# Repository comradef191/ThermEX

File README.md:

# ThermEX
A BlackPill powered expansion board for Klipper 3D printers, allowing the use of numerous additional Thermistors.

- Can be stacked ontop of or underneith Nyoomies using appropiate spacers
- OpenSource Hardware, licensed under the [OHLv2-S](https://opensource.org/license/cern-ohl-s)
- 10 thermistors wired directly to the STM32
- 16 additional thermistors wired up via 4 ADS1115 ICs
- Powered directly from the USB port
- Uses an ultra-low-noise [TPS7A2033](https://www.ti.com/product/TPS7A20/part-details/TPS7A2033PDBVR) 300mA 3.3v voltage regulator to power all expansion headers and the ADS1115s
- Features native support for the STM32F4x1 BlackPill, with the unused extra GPIO being broken out to a labelled expansion header alongside 3v3 & GND
- Breaks out the I2C2 & I2C3 busses to a pair of dedicated 4-pin JST-XH connectors
- Breaks out the SPI2 bus to a dedicated header, alongside PB12 to act as chip-select

# NOTICE
if you are ordering a batch of PCBs, please for the love of god please use the pre-made gerber files in the [Releases tab](https://github.com/comradef191/ThermEX/releases) instead of downloading the repo, ignoring KiCADs warning you haven't got [a font installed](https://github.com/ETBCOR/nasin-nanpa), and then exporting your own files which both have the I2C bus shorted out (rendering only 10 thermistor ports usable) due to the missing font breaking artwork on the copper layer plus has had markings crediting me destroyed.

## Vendors
UK / EU
- None... yet!

Contact me on Discord if you want to add yourself to this list!

## Bill of Materials
This BoM lists exclusively through-hole components, as SMD components will be assembled for you by JLCPCB
|  Component         |QTY | Cost  |  Comment               |  Sourcing URL                                                                                                |
|--------------------|----|-------|------------------------|--------------------------------------------------------------------------------------------------------------|
|JST-XH 2-Pin        | 26 | $0.39 | Thermistor Ports       | https://www.lcsc.com/product-detail/Wire-To-Board-Connector_DEALON-XH-D-2A_C5160911.html                     |
|JST-XH 4-Pin        | 2  | $0.52 | I2C Ports              | https://www.lcsc.com/product-detail/Wire-To-Board-Connector_JST-B4B-XH-A-LF-SN_C144395.html                  |
|2.54 Socket, 1x20   | 2  | $0.81 | STM32 Socket           | https://www.lcsc.com/product-detail/Female-Headers_Shenzhen-Kinghelm-Elec-KH-2-54FH-1X20P-H8-5_C2905423.html |
|2.54 Header, 2x5    | 3  | $0.40 | GPIO; Cut-Down for SPI | https://www.lcsc.com/product-detail/Pin-Headers_HanElectricity-2541WV-2x05P_C5383106.html                    |
|STM32F401 Blackpill | 1  | $3.25 | Main controller        | https://www.aliexpress.com/item/1005006127461676.html                                                        |

# Gallery
*As of 09APR25 no ThermEX26 boards have been produced, thus only KiCad Renders are present currently*

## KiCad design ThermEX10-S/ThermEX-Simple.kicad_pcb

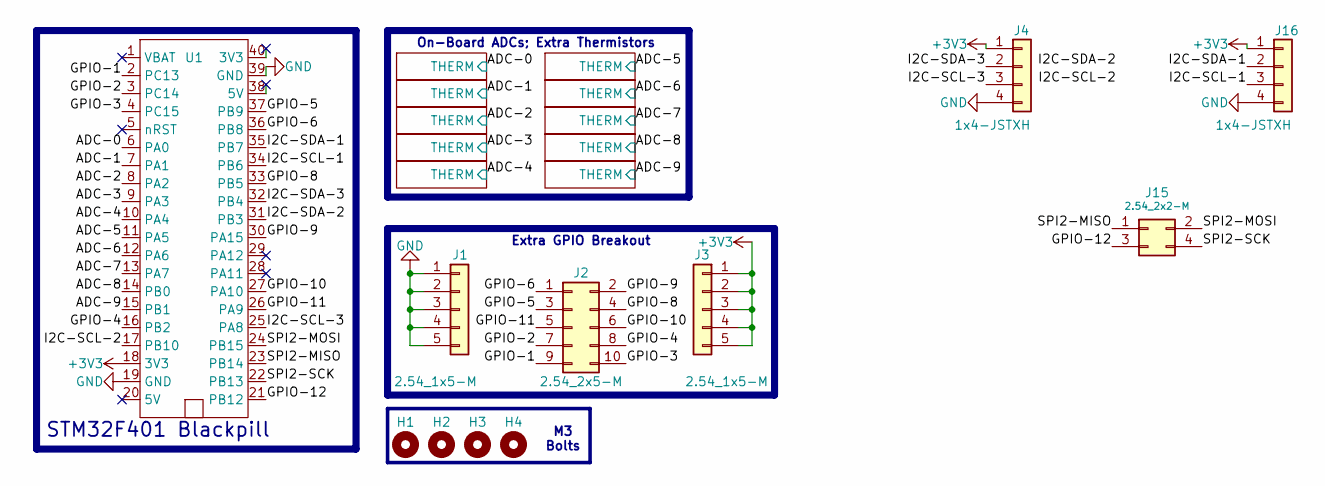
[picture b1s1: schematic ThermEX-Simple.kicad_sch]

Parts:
H1, H2, H3, H4: MountingHole; M3 Mounting Hole ~ Classic - No Keepout
J1, J3: 2.54_1x5-M; PinHeader_1x05_P2.54mm_Vertical
J2: 2.54_2x5-M; PinHeader_2x05_P2.54mm_Vertical
J4, J16: 1x4-JSTXH; JST_XH_B4B-XH-A_1x04_P2.50mm_Vertical
J15: 2.54_2x2-M; PinHeader_2x02_P2.54mm_Vertical
U1: STM32F401 Blackpill; Socketed MCU - STM32 BlackPill

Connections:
+3V3: J3.1, J3.2, J3.3, J3.4, J3.5, J4.1, J16.1, U1.18 (3V3); also elsewhere on the board
/ADC-0: U1.6 (PA0); also elsewhere on the board
/ADC-1: U1.7 (PA1); also elsewhere on the board
/ADC-2: U1.8 (PA2); also elsewhere on the board
/ADC-3: U1.9 (PA3); also elsewhere on the board
/ADC-4: U1.10 (PA4); also elsewhere on the board
/ADC-5: U1.11 (PA5); also elsewhere on the board
/ADC-6: U1.12 (PA6); also elsewhere on the board
/ADC-7: U1.13 (PA7); also elsewhere on the board
/ADC-8: U1.14 (PB0); also elsewhere on the board
/ADC-9: U1.15 (PB1); also elsewhere on the board
/GPIO-1: J2.9, U1.2 (PC13)
/GPIO-2: J2.7, U1.3 (PC14)
/GPIO-3: J2.10, U1.4 (PC15)
/GPIO-4: J2.8, U1.16 (PB2)
/GPIO-5: J2.3, U1.37 (PB9)
/GPIO-6: J2.1, U1.36 (PB8)
/GPIO-8: J2.4, U1.33 (PB5)
/GPIO-9: J2.2, U1.30 (PA15)
/GPIO-10: J2.6, U1.27 (PA10)
/GPIO-11: J2.5, U1.26 (PA9)
/GPIO-12: J15.3, U1.21 (PB12)
/I2C-SCL-1: J16.3, U1.34 (PB6)
/I2C-SCL-2: U1.17 (PB10)
/I2C-SCL-3: J4.3, U1.25 (PA8)
/I2C-SDA-1: J16.2, U1.35 (PB7)
/I2C-SDA-2: U1.31 (PB3)
/I2C-SDA-3: J4.2, U1.32 (PB4)
/SPI2-MISO: J15.1, U1.23 (PB14)
/SPI2-MOSI: J15.2, U1.24 (PB15)
/SPI2-SCK: J15.4, U1.22 (PB13)
GND: J1.1, J1.2, J1.3, J1.4, J1.5, J4.4, J16.4, U1.19 (GND), U1.39 (GND); also elsewhere on the board

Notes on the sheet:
STM32F401 Blackpill
M3 Bolts
Extra GPIO Breakout
On-Board ADCs; Extra Thermistors

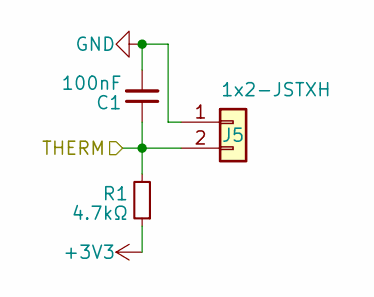
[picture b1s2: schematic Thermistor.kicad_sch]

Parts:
C1: 100nF; C_Disc_D5.0mm_W2.5mm_P5.00mm
J5: 1x2-JSTXH; JST-XH_1x02-V ~ Custom
R1: 4.7kΩ; R_Axial_DIN0207_L6.3mm_D2.5mm_P10.16mm_Horizontal

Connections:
+3V3: R1.1; also elsewhere on the board
/ADC-0: C1.1, J5.2, R1.2; also elsewhere on the board
GND: C1.2, J5.1; also elsewhere on the board

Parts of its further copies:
C2, C3, C4, C5, C6, C7, C8, C9, C10: 100nF; C_Disc_D5.0mm_W2.5mm_P5.00mm
J6, J7, J8, J9, J10, J11, J12, J13, J14: 1x2-JSTXH; JST-XH_1x02-V ~ Custom
R2, R3, R4, R5, R6, R7, R8, R9, R10: 4.7kΩ; R_Axial_DIN0207_L6.3mm_D2.5mm_P10.16mm_Horizontal

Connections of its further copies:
+3V3: R2.1, R3.1, R4.1, R5.1, R6.1, R7.1, R8.1, R9.1, R10.1; also elsewhere on the board
/ADC-1: C2.1, J6.2, R2.2; also elsewhere on the board
/ADC-2: C3.1, J7.2, R3.2; also elsewhere on the board
/ADC-3: C4.1, J8.2, R4.2; also elsewhere on the board
/ADC-4: C5.1, J9.2, R5.2; also elsewhere on the board
/ADC-5: C6.1, J10.2, R6.2; also elsewhere on the board
/ADC-6: C7.1, J11.2, R7.2; also elsewhere on the board
/ADC-7: C8.1, J12.2, R8.2; also elsewhere on the board
/ADC-8: C9.1, J13.2, R9.2; also elsewhere on the board
/ADC-9: C10.1, J14.2, R10.2; also elsewhere on the board
GND: C2.2, C3.2, C4.2, C5.2, C6.2, C7.2, C8.2, C9.2, C10.2, J6.1, J7.1, J8.1, J9.1, J10.1, J11.1, J12.1, J13.1, J14.1; also elsewhere on the board

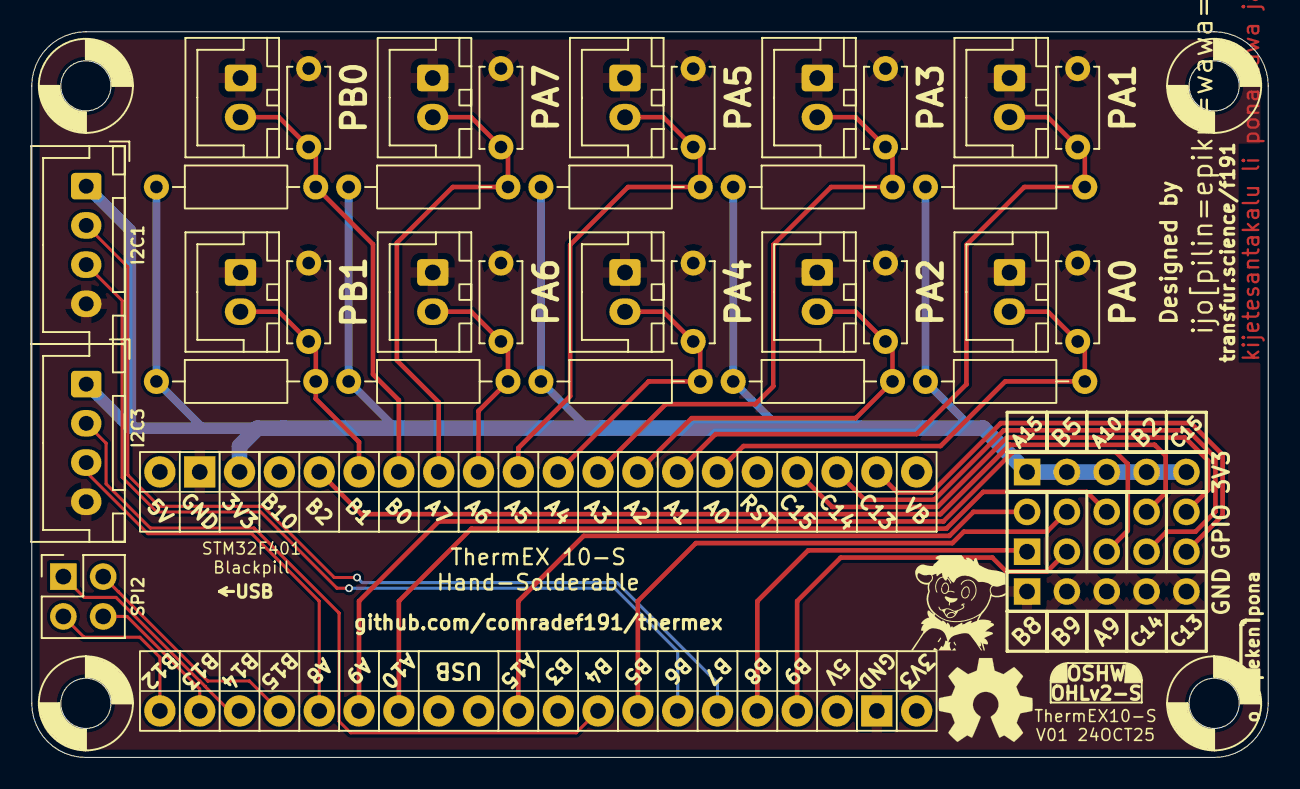
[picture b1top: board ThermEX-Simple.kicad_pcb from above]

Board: 2 copper layers, 78.9 x 46.3 mm, 41 parts (0 on the bottom side), 30 nets.

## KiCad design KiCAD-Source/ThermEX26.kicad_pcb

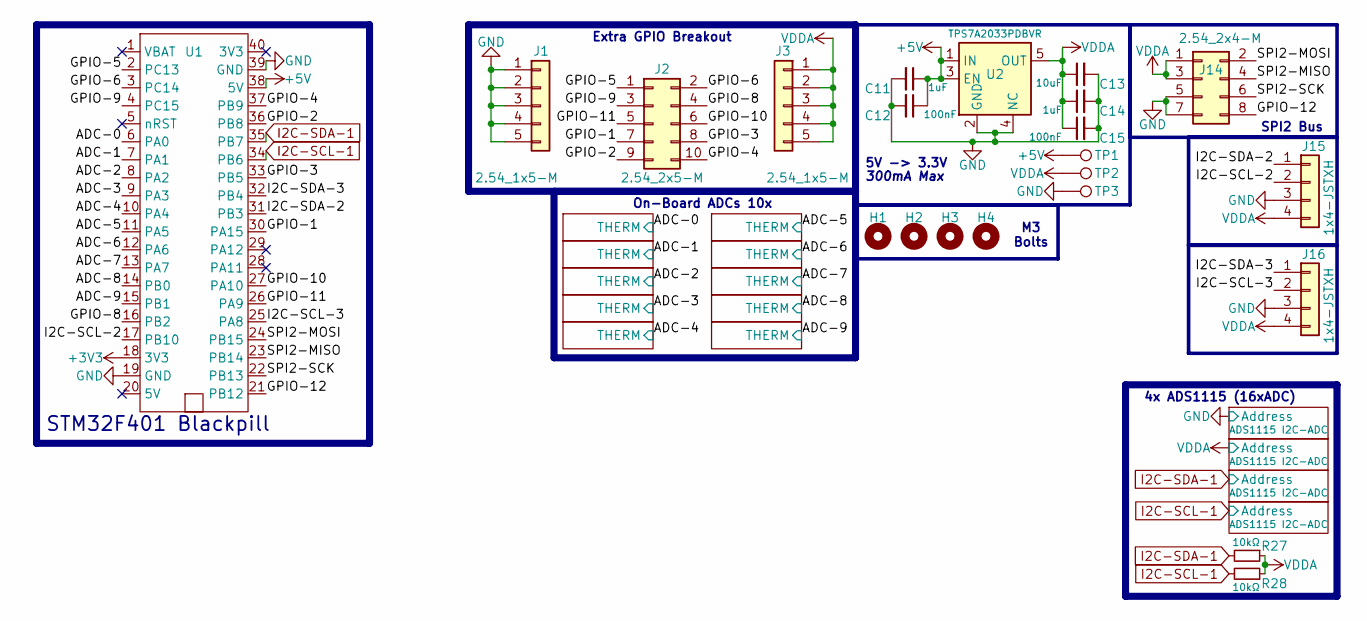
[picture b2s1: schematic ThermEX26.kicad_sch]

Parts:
C11, C14: 1uF; C_0603_1608Metric; LCSC C15849
C12, C15: 100nF; C_0603_1608Metric; LCSC C14663
C13: 10uF; C_0603_1608Metric; LCSC C96446
H1, H2, H3, H4: M3 Mounting Hole; M3 Mounting Hole ~ Classic
J1, J3: 2.54_1x5-M; PinHeader_1x05_P2.54mm_Vertical
J2: 2.54_2x5-M; PinHeader_2x05_P2.54mm_Vertical
J14: 2.54_2x4-M; PinHeader_2x04_P2.54mm_Vertical
J15, J16: 1x4-JSTXH; JST_XH_B4B-XH-A_1x04_P2.50mm_Vertical; LCSC C144395
R27, R28: 10kΩ; R_0603_1608Metric_Pad0.98x0.95mm_HandSolder; LCSC C25804
TP1, TP2, TP3: TestPoint; TestPoint_THTPad_D1.5mm_Drill0.7mm
U1: Socketed MCU - STM32 BlackPill
U2: TPS7A2033PDBVR; SOT-23-5; LCSC C2862740

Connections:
+3V3: U1.18 (3V3); also elsewhere on the board
+5V: C11.1, C12.1, TP1.1, U1.38 (5V), U2.1 (IN), U2.3 (EN)
/ADC-0: U1.6 (PA0); also elsewhere on the board
/ADC-1: U1.7 (PA1); also elsewhere on the board
/ADC-2: U1.8 (PA2); also elsewhere on the board
/ADC-3: U1.9 (PA3); also elsewhere on the board
/ADC-4: U1.10 (PA4); also elsewhere on the board
/ADC-5: U1.11 (PA5); also elsewhere on the board
/ADC-6: U1.12 (PA6); also elsewhere on the board
/ADC-7: U1.13 (PA7); also elsewhere on the board
/ADC-8: U1.14 (PB0); also elsewhere on the board
/ADC-9: U1.15 (PB1); also elsewhere on the board
/GPIO-1: J2.7, U1.30 (PA15)
/GPIO-2: J2.9, U1.36 (PB8)
/GPIO-3: J2.8, U1.33 (PB5)
/GPIO-4: J2.10, U1.37 (PB9)
/GPIO-5: J2.1, U1.2 (PC13)
/GPIO-6: J2.2, U1.3 (PC14)
/GPIO-8: J2.4, U1.16 (PB2)
/GPIO-9: J2.3, U1.4 (PC15)
/GPIO-10: J2.6, U1.27 (PA10)
/GPIO-11: J2.5, U1.26 (PA9)
/GPIO-12: J14.8, U1.21 (PB12)
/I2C-SCL-2: J15.2, U1.17 (PB10)
/I2C-SCL-3: J16.2, U1.25 (PA8)
/I2C-SDA-2: J15.1, U1.31 (PB3)
/I2C-SDA-3: J16.1, U1.32 (PB4)
/SPI2-MISO: J14.4, U1.23 (PB14)
/SPI2-MOSI: J14.2, U1.24 (PB15)
/SPI2-SCK: J14.6, U1.22 (PB13)
GND: C11.2, C12.2, C13.2, C14.2, C15.2, J1.1, J1.2, J1.3, J1.4, J1.5, J14.5, J14.7, J15.3, J16.3, TP3.1, U1.19 (GND), U1.39 (GND), U2.2 (GND), U2.4 (NC); also elsewhere on the board
I2C-SCL-1: R28.2, U1.34 (PB6); also elsewhere on the board
I2C-SDA-1: R27.2, U1.35 (PB7); also elsewhere on the board
VDDA: C13.1, C14.1, C15.1, J3.1, J3.2, J3.3, J3.4, J3.5, J14.1, J14.3, J15.4, J16.4, R27.1, R28.1, TP2.1, U2.5 (OUT); also elsewhere on the board

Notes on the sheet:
M3 Bolts
300mA Max
STM32F401 Blackpill
SPI2 Bus
Extra GPIO Breakout
On-Board ADCs 10x
4x ADS1115 (16xADC)
5V -> 3.3V

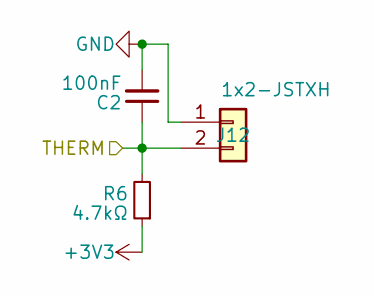
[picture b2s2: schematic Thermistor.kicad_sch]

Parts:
C2: 100nF; C_0603_1608Metric; LCSC C14663
J12: 1x2-JSTXH; JST-XH_1x02-V ~ Custom; LCSC C5160911
R6: 4.7kΩ; R_0603_1608Metric; LCSC C23162

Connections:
+3V3: R6.1; also elsewhere on the board
/ADC-0: C2.1, J12.2, R6.2; also elsewhere on the board
GND: C2.2, J12.1; also elsewhere on the board

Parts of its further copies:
C1, C3, C4, C5, C6, C7, C8, C9, C10: 100nF; C_0603_1608Metric; LCSC C14663
J4, J5, J6, J7, J8, J9, J10, J11, J13: 1x2-JSTXH; JST-XH_1x02-V ~ Custom; LCSC C5160911
R1, R2, R3, R4, R5, R7, R8, R9, R10: 4.7kΩ; R_0603_1608Metric; LCSC C23162

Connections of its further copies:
+3V3: R1.1, R2.1, R3.1, R4.1, R5.1, R7.1, R8.1, R9.1, R10.1; also elsewhere on the board
/ADC-1: C1.1, J4.2, R1.2; also elsewhere on the board
/ADC-2: C3.1, J5.2, R2.2; also elsewhere on the board
/ADC-3: C4.1, J6.2, R3.2; also elsewhere on the board
/ADC-4: C5.1, J7.2, R4.2; also elsewhere on the board
/ADC-5: C8.1, J8.2, R9.2; also elsewhere on the board
/ADC-6: C6.1, J9.2, R5.2; also elsewhere on the board
/ADC-7: C7.1, J10.2, R7.2; also elsewhere on the board
/ADC-8: C9.1, J11.2, R8.2; also elsewhere on the board
/ADC-9: C10.1, J13.2, R10.2; also elsewhere on the board
GND: C1.2, C3.2, C4.2, C5.2, C6.2, C7.2, C8.2, C9.2, C10.2, J4.1, J5.1, J6.1, J7.1, J8.1, J9.1, J10.1, J11.1, J13.1; also elsewhere on the board

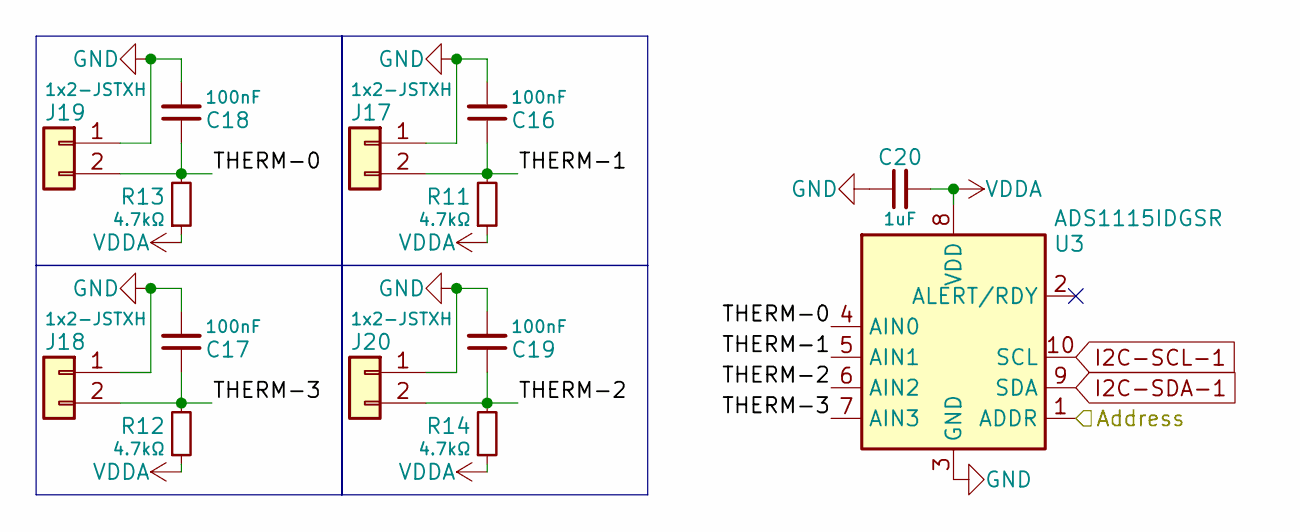
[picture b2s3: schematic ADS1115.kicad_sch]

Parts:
C16, C17, C18, C19: 100nF; C_0603_1608Metric; LCSC C14663
C20: 1uF; C_0603_1608Metric; LCSC C15849
J17, J18, J19, J20: 1x2-JSTXH; JST-XH_1x02-V ~ Custom; LCSC C5160911
R11, R12, R13, R14: 4.7kΩ; R_0603_1608Metric; LCSC C23162
U3: ADS1115IDGSR; VSSOP-10_3x3mm_P0.5mm; LCSC C37593

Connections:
/ADSChip 1/THERM-0: C18.1, J19.2, R13.2, U3.4 (AIN0)
/ADSChip 1/THERM-1: C16.1, J17.2, R11.2, U3.5 (AIN1)
/ADSChip 1/THERM-2: C19.1, J20.2, R14.2, U3.6 (AIN2)
/ADSChip 1/THERM-3: C17.1, J18.2, R12.2, U3.7 (AIN3)
GND: C16.2, C17.2, C18.2, C19.2, C20.1, J17.1, J18.1, J19.1, J20.1, U3.1 (ADDR), U3.3 (GND); also elsewhere on the board
I2C-SCL-1: U3.10 (SCL); also elsewhere on the board
I2C-SDA-1: U3.9 (SDA); also elsewhere on the board
VDDA: C20.2, R11.1, R12.1, R13.1, R14.1, U3.8 (VDD); also elsewhere on the board

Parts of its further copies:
C21, C22, C23, C24, C26, C27, C28, C29, C31, C32, C33, C34: 100nF; C_0603_1608Metric; LCSC C14663
C25, C30, C35: 1uF; C_0603_1608Metric; LCSC C15849
J21, J22, J23, J24, J25, J26, J27, J28, J29, J30, J31, J32: 1x2-JSTXH; JST-XH_1x02-V ~ Custom; LCSC C5160911
R15, R16, R17, R18, R19, R20, R21, R22, R23, R24, R25, R26: 4.7kΩ; R_0603_1608Metric; LCSC C23162
U4, U5, U6: ADS1115IDGSR; VSSOP-10_3x3mm_P0.5mm; LCSC C37593

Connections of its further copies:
/ADSChip 2/THERM-0: C23.1, J23.2, R17.2, U4.4 (AIN0)
/ADSChip 2/THERM-1: C21.1, J21.2, R15.2, U4.5 (AIN1)
/ADSChip 2/THERM-2: C24.1, J24.2, R18.2, U4.6 (AIN2)
/ADSChip 2/THERM-3: C22.1, J22.2, R16.2, U4.7 (AIN3)
/ADSChip 3/THERM-0: C28.1, J27.2, R21.2, U5.4 (AIN0)
/ADSChip 3/THERM-1: C26.1, J25.2, R19.2, U5.5 (AIN1)
/ADSChip 3/THERM-2: C29.1, J28.2, R22.2, U5.6 (AIN2)
/ADSChip 3/THERM-3: C27.1, J26.2, R20.2, U5.7 (AIN3)
/ADSChip 4/THERM-0: C33.1, J31.2, R25.2, U6.4 (AIN0)
/ADSChip 4/THERM-1: C31.1, J29.2, R23.2, U6.5 (AIN1)
/ADSChip 4/THERM-2: C34.1, J32.2, R26.2, U6.6 (AIN2)
/ADSChip 4/THERM-3: C32.1, J30.2, R24.2, U6.7 (AIN3)
GND: C21.2, C22.2, C23.2, C24.2, C25.1, C26.2, C27.2, C28.2, C29.2, C30.1, C31.2, C32.2, C33.2, C34.2, C35.1, J21.1, J22.1, J23.1, J24.1, J25.1, J26.1, J27.1, J28.1, J29.1, J30.1, J31.1, J32.1, U4.3 (GND), U5.3 (GND), U6.3 (GND); also elsewhere on the board
I2C-SCL-1: U4.10 (SCL), U5.10 (SCL), U6.1 (ADDR), U6.10 (SCL); also elsewhere on the board
I2C-SDA-1: U4.9 (SDA), U5.1 (ADDR), U5.9 (SDA), U6.9 (SDA); also elsewhere on the board
VDDA: C25.2, C30.2, C35.2, R15.1, R16.1, R17.1, R18.1, R19.1, R20.1, R21.1, R22.1, R23.1, R24.1, R25.1, R26.1, U4.1 (ADDR), U4.8 (VDD), U5.8 (VDD), U6.8 (VDD); also elsewhere on the board

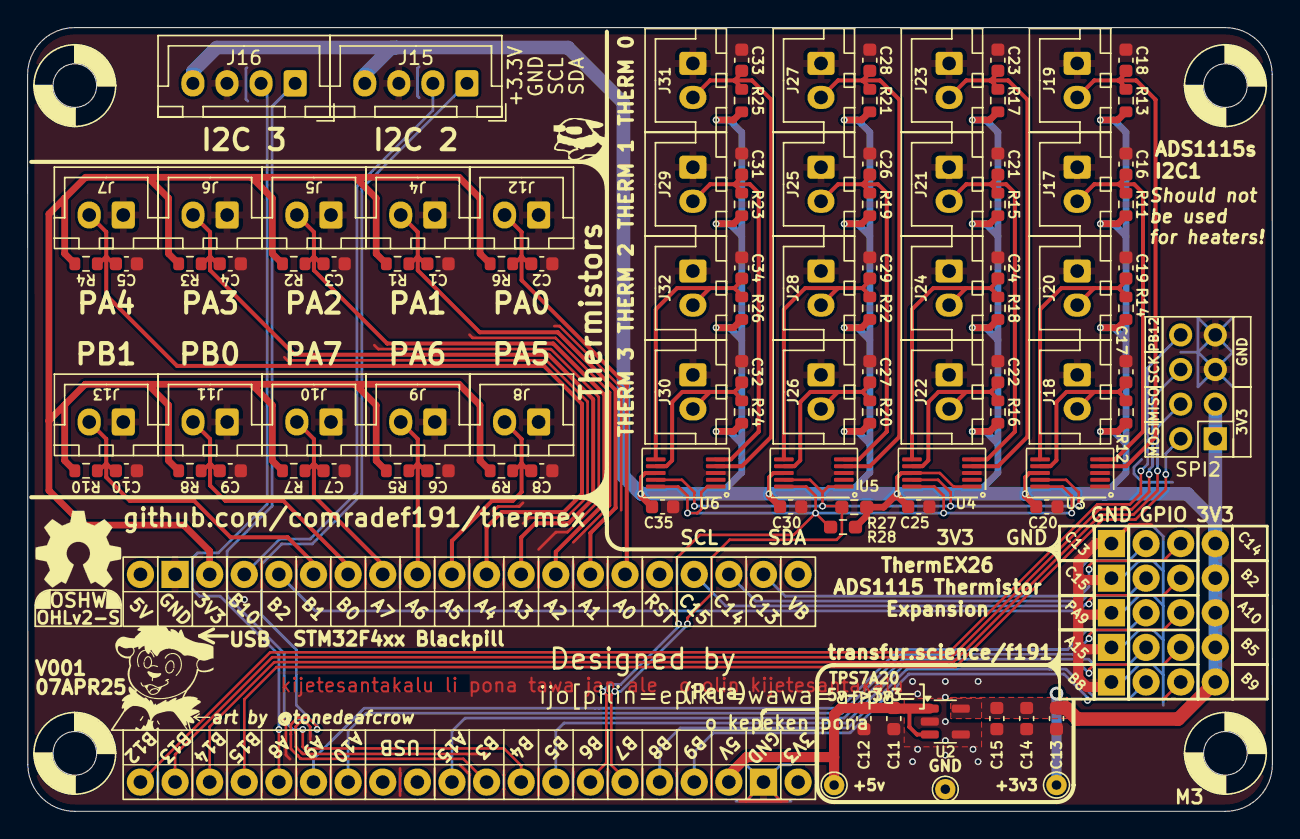
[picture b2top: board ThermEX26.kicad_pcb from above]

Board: 2 copper layers, 91.3 x 57.5 mm, 108 parts (0 on the bottom side), 50 nets.

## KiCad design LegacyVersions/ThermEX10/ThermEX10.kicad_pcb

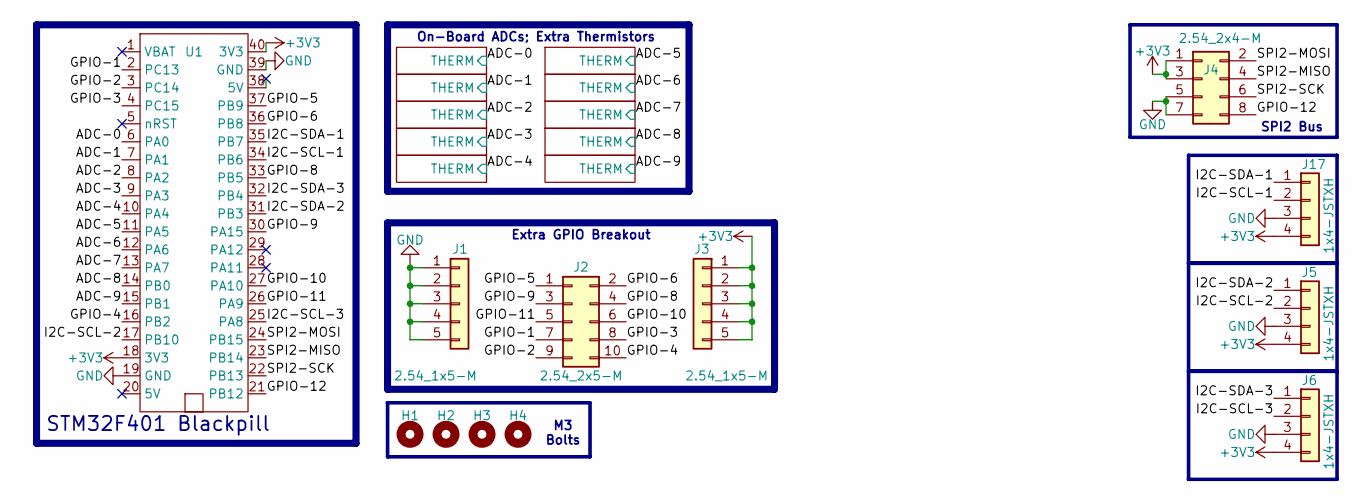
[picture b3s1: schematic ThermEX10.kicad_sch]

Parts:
H1, H2, H3, H4: M3 Mounting Hole; M3 Mounting Hole ~ Classic
J1, J3: 2.54_1x5-M; PinHeader_1x05_P2.54mm_Vertical
J2: 2.54_2x5-M; PinHeader_2x05_P2.54mm_Vertical
J4: 2.54_2x4-M; PinHeader_2x04_P2.54mm_Vertical
J5, J6, J17: 1x4-JSTXH; JST_XH_B4B-XH-A_1x04_P2.50mm_Vertical; LCSC C144395
U1: Socketed MCU - STM32 BlackPill

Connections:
+3V3: J3.1, J3.2, J3.3, J3.4, J3.5, J4.1, J4.3, J5.4, J6.4, J17.4, U1.18 (3V3), U1.40 (3V3); also elsewhere on the board
/ADC-0: U1.6 (PA0); also elsewhere on the board
/ADC-1: U1.7 (PA1); also elsewhere on the board
/ADC-2: U1.8 (PA2); also elsewhere on the board
/ADC-3: U1.9 (PA3); also elsewhere on the board
/ADC-4: U1.10 (PA4); also elsewhere on the board
/ADC-5: U1.11 (PA5); also elsewhere on the board
/ADC-6: U1.12 (PA6); also elsewhere on the board
/ADC-7: U1.13 (PA7); also elsewhere on the board
/ADC-8: U1.14 (PB0); also elsewhere on the board
/ADC-9: U1.15 (PB1); also elsewhere on the board
/GPIO-1: J2.7, U1.2 (PC13)
/GPIO-2: J2.9, U1.3 (PC14)
/GPIO-3: J2.8, U1.4 (PC15)
/GPIO-4: J2.10, U1.16 (PB2)
/GPIO-5: J2.1, U1.37 (PB9)
/GPIO-6: J2.2, U1.36 (PB8)
/GPIO-8: J2.4, U1.33 (PB5)
/GPIO-9: J2.3, U1.30 (PA15)
/GPIO-10: J2.6, U1.27 (PA10)
/GPIO-11: J2.5, U1.26 (PA9)
/GPIO-12: J4.8, U1.21 (PB12)
/I2C-SCL-1: J17.2, U1.34 (PB6)
/I2C-SCL-2: J5.2, U1.17 (PB10)
/I2C-SCL-3: J6.2, U1.25 (PA8)
/I2C-SDA-1: J17.1, U1.35 (PB7)
/I2C-SDA-2: J5.1, U1.31 (PB3)
/I2C-SDA-3: J6.1, U1.32 (PB4)
/SPI2-MISO: J4.4, U1.23 (PB14)
/SPI2-MOSI: J4.2, U1.24 (PB15)
/SPI2-SCK: J4.6, U1.22 (PB13)
GND: J1.1, J1.2, J1.3, J1.4, J1.5, J4.5, J4.7, J5.3, J6.3, J17.3, U1.19 (GND), U1.39 (GND); also elsewhere on the board

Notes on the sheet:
M3 Bolts
SPI2 Bus
STM32F401 Blackpill
Extra GPIO Breakout
On-Board ADCs; Extra Thermistors

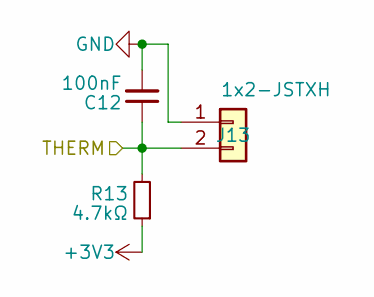
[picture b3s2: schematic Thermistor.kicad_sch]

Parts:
C12: 100nF; C_0603_1608Metric; LCSC C14663
J13: 1x2-JSTXH; JST-XH_1x02-V ~ Custom; LCSC C5160911
R13: 4.7kΩ; R_0603_1608Metric; LCSC C2989672

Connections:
+3V3: R13.1; also elsewhere on the board
/ADC-6: C12.1, J13.2, R13.2; also elsewhere on the board
GND: C12.2, J13.1; also elsewhere on the board

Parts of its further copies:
C6, C7, C8, C9, C10, C11, C13, C14, C15: 100nF; C_0603_1608Metric; LCSC C14663
J7, J8, J9, J10, J11, J12, J14, J15, J16: 1x2-JSTXH; JST-XH_1x02-V ~ Custom; LCSC C5160911
R7, R8, R9, R10, R11, R12, R14, R15, R16: 4.7kΩ; R_0603_1608Metric; LCSC C2989672

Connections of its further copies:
+3V3: R7.1, R8.1, R9.1, R10.1, R11.1, R12.1, R14.1, R15.1, R16.1; also elsewhere on the board
/ADC-0: C6.1, J7.2, R7.2; also elsewhere on the board
/ADC-1: C7.1, J8.2, R8.2; also elsewhere on the board
/ADC-2: C8.1, J9.2, R9.2; also elsewhere on the board
/ADC-3: C9.1, J10.2, R10.2; also elsewhere on the board
/ADC-4: C10.1, J11.2, R11.2; also elsewhere on the board
/ADC-5: C11.1, J12.2, R12.2; also elsewhere on the board
/ADC-7: C13.1, J14.2, R14.2; also elsewhere on the board
/ADC-8: C14.1, J15.2, R15.2; also elsewhere on the board
/ADC-9: C15.1, J16.2, R16.2; also elsewhere on the board
GND: C6.2, C7.2, C8.2, C9.2, C10.2, C11.2, C13.2, C14.2, C15.2, J7.1, J8.1, J9.1, J10.1, J11.1, J12.1, J14.1, J15.1, J16.1; also elsewhere on the board

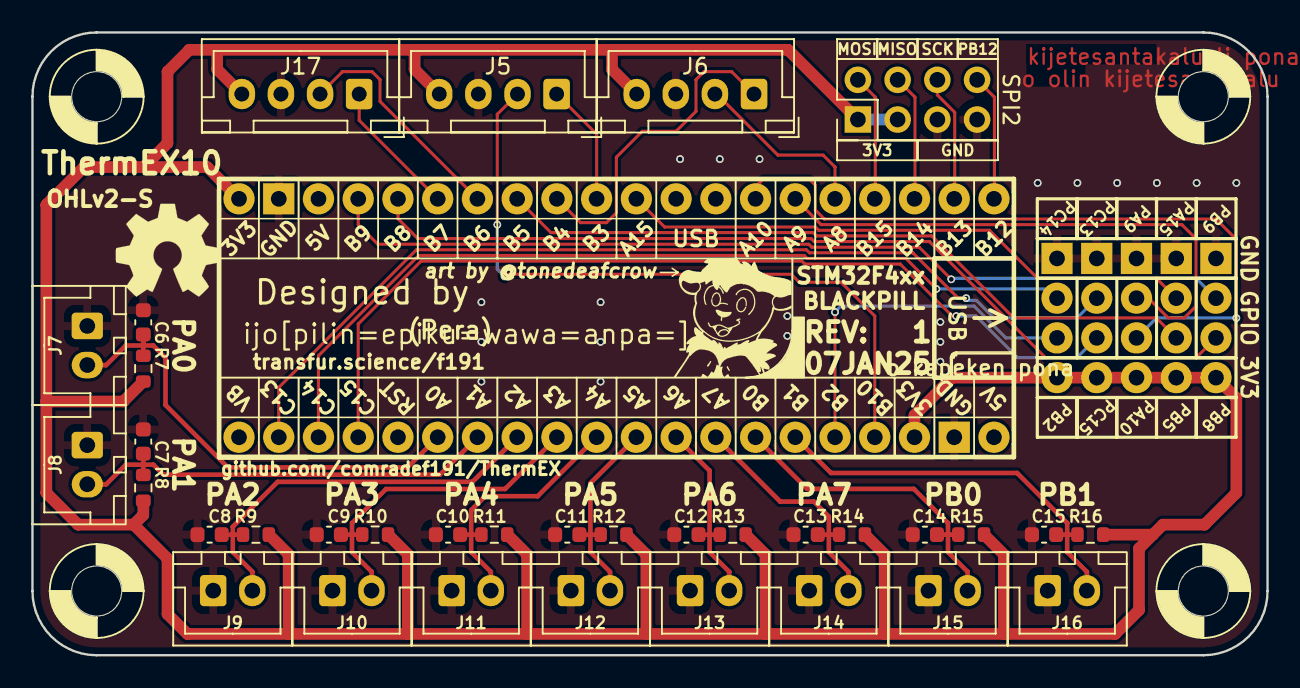
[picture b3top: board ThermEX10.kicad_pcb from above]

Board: 2 copper layers, 79.0 x 39.8 mm, 42 parts (0 on the bottom side), 32 nets.

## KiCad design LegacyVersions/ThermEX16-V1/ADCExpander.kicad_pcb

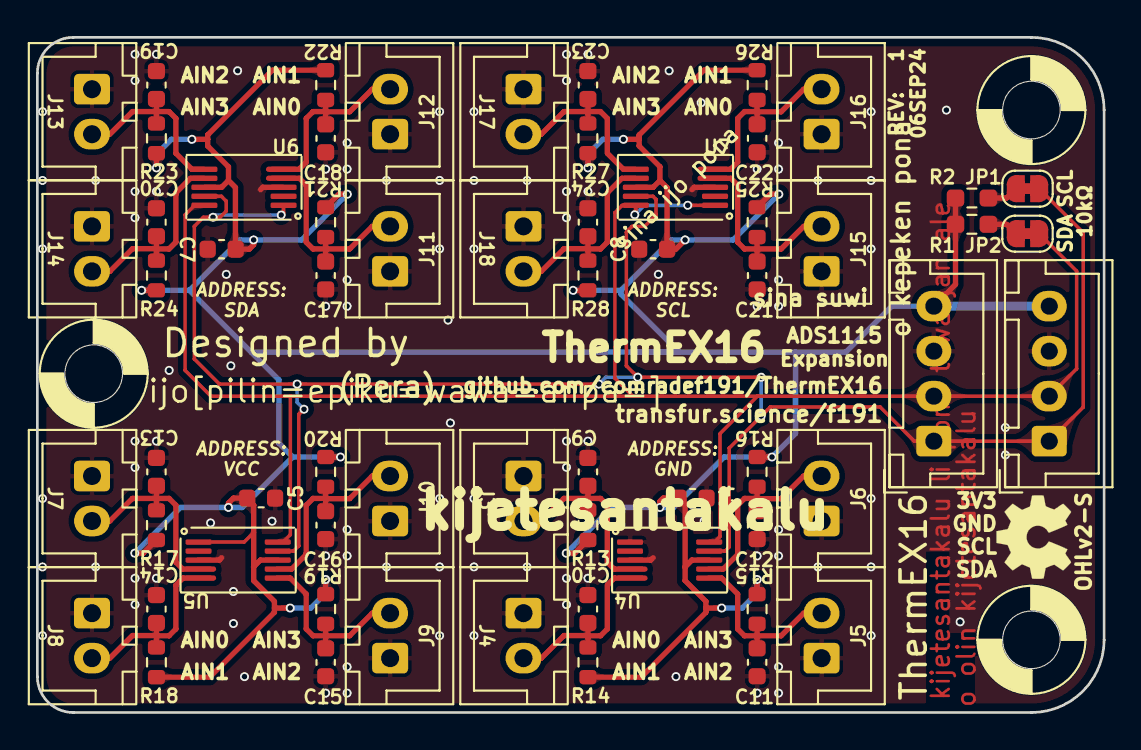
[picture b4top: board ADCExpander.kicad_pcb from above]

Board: 2 copper layers, 59.3 x 37.5 mm, 65 parts (0 on the bottom side), 22 nets.

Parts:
C4, C5, C7, C8: 1uF; C_0603_1608Metric
C9, C10, C11, C12, C13, C14, C15, C16, C17, C18, C19, C20, C21, C22, C23, C24: 100nF; C_0603_1608Metric
H1, H2, H3: MountingHole; M3 Mounting Hole ~ Classic
J1, J2: Conn_01x04; JST_XH_B4B-XH-A_1x04_P2.50mm_Vertical
J3, J4, J5, J6, J7, J8, J9, J10, J11, J12, J13, J14, J15, J16, J17, J18: 1x2-JSTXH; JST-XH_1x02-V ~ Custom
JP1, JP2: SolderJumper_2_Bridged; SolderJumper-2_P1.3mm_Bridged_RoundedPad1.0x1.5mm
R1, R2: 10kΩ; R_0603_1608Metric_Pad0.98x0.95mm_HandSolder
R13, R14, R15, R16, R17, R18, R19, R20, R21, R22, R23, R24, R25, R26, R27, R28: 4.7kΩ; R_0603_1608Metric
U4, U5, U6, U7: ADS1115IDGSR; VSSOP-10_3x3mm_P0.5mm

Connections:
/I2C0-SCL: J1.2, J2.2, JP2.2 (B), U4.10 (SCL), U5.10 (SCL), U6.10 (SCL), U7.1 (ADDR), U7.10 (SCL)
/I2C0-SDA: J1.1, J2.1, JP1.2 (B), U4.9 (SDA), U5.9 (SDA), U6.1 (ADDR), U6.9 (SDA), U7.9 (SDA)
/THERM-1: C9.1, J3.2, R13.2, U4.4 (AIN0)
/THERM-2: C10.1, J4.2, R14.2, U4.5 (AIN1)
/THERM-3: C11.1, J5.2, R15.2, U4.6 (AIN2)
/THERM-4: C12.1, J6.2, R16.2, U4.7 (AIN3)
/THERM-5: C13.1, J7.2, R17.2, U5.4 (AIN0)
/THERM-6: C14.1, J8.2, R18.2, U5.5 (AIN1)
/THERM-7: C15.1, J9.2, R19.2, U5.6 (AIN2)
/THERM-8: C16.1, J10.2, R20.2, U5.7 (AIN3)
/THERM-9: C17.1, J11.2, R21.2, U6.4 (AIN0)
/THERM-10: C18.1, J12.2, R22.2, U6.5 (AIN1)
/THERM-11: C19.1, J13.2, R23.2, U6.6 (AIN2)
/THERM-12: C20.1, J14.2, R24.2, U6.7 (AIN3)
/THERM-13: C21.1, J15.2, R25.2, U7.4 (AIN0)
/THERM-14: C22.1, J16.2, R26.2, U7.5 (AIN1)
/THERM-15: C23.1, J17.2, R27.2, U7.6 (AIN2)
/THERM-16: C24.1, J18.2, R28.2, U7.7 (AIN3)
GNDA: C4.1, C5.1, C7.1, C8.1, C9.2, C10.2, C11.2, C12.2, C13.2, C14.2, C15.2, C16.2, C17.2, C18.2, C19.2, C20.2, C21.2, C22.2, C23.2, C24.2, J1.3, J2.3, J3.1, J4.1, J5.1, J6.1, J7.1, J8.1, J9.1, J10.1, J11.1, J12.1, J13.1, J14.1, J15.1, J16.1, J17.1, J18.1, U4.1 (ADDR), U4.3 (GND), U5.3 (GND), U6.3 (GND), U7.3 (GND)
unnamed: JP1.1 (A), R2.2
unnamed: JP2.1 (A), R1.2
VDDA: C4.2, C5.2, C7.2, C8.2, J1.4, J2.4, R1.1, R2.1, R13.1, R14.1, R15.1, R16.1, R17.1, R18.1, R19.1, R20.1, R21.1, R22.1, R23.1, R24.1, R25.1, R26.1, R27.1, R28.1, U4.8 (VDD), U5.1 (ADDR), U5.8 (VDD), U6.8 (VDD), U7.8 (VDD)

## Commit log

2025-04-09 Add License
2025-04-09 Add Legacy Versions
2025-04-09 Add ThermEX26
2025-04-09 Added titleblocks to drawings
2025-04-09 Add PDF of schematic & .steps of PCB
2025-06-27 im so tired.
    Add warning about what happens when you ignore KiCads warning you're missing a font and export your own files despite said warning.
2025-10-24 Create Project
2025-10-24 Simple ThermEX
2025-10-24 Reorganise folders
2025-10-24 Quick Fix

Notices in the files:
ThermEX26/ADS1115.kicad_sch:
CERN OHL v2 - S
